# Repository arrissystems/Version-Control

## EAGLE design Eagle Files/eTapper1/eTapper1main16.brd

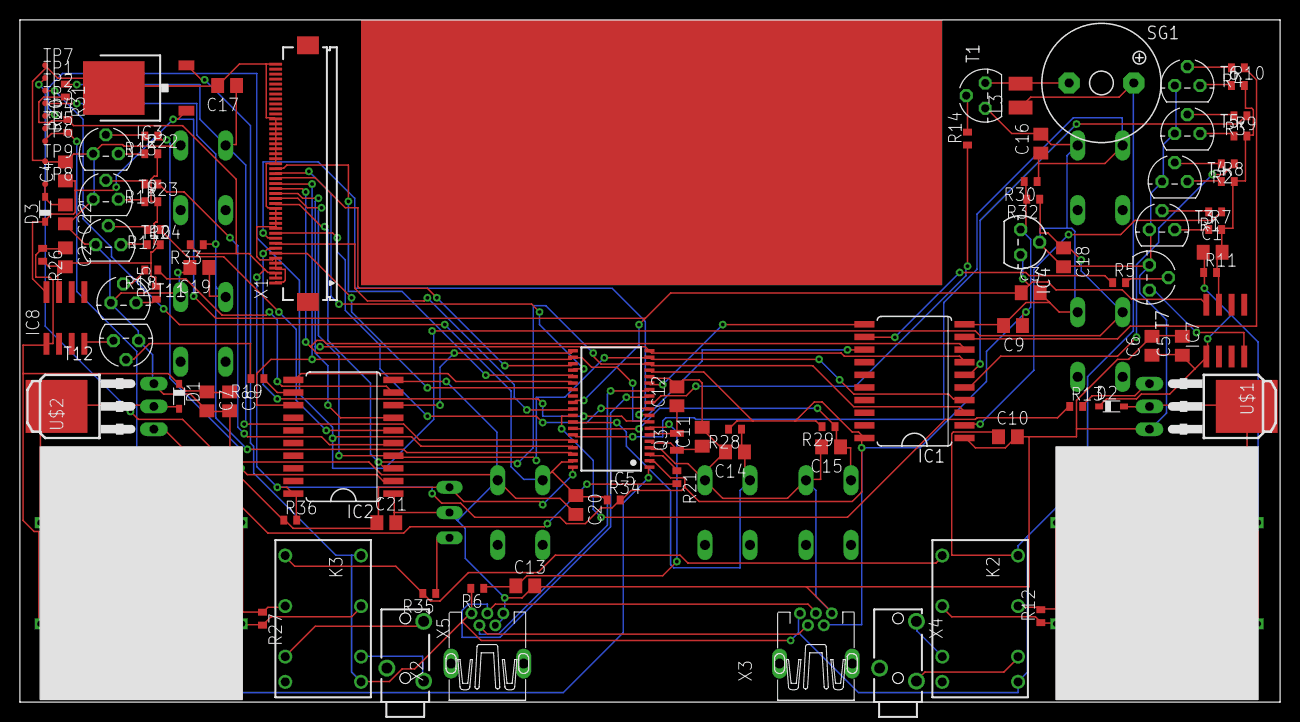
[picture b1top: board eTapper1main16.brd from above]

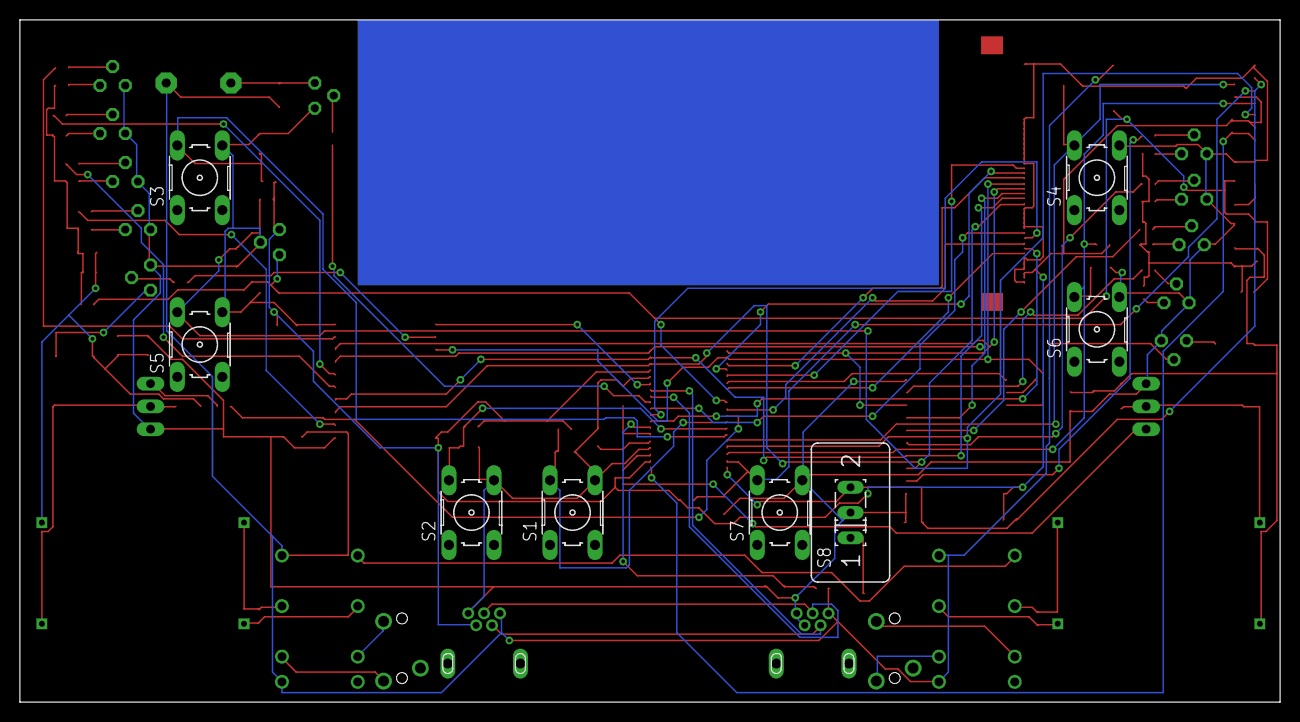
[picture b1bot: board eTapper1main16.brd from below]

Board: 2 copper layers, 126.7 x 68.6 mm, 110 parts (8 on the bottom side), 87 nets.

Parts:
C1, C2: .01uF; C0805
C3, C4: C0805
C5, C8: 3.3uF; C0805
C6, C7, C22: 220uF; C0805
C9, C10: 47uF; C0805
C11, C12: 12pF; C0805
C13: 1 uF; C0805
C14, C15, C16, C17, C18, C19, C20, C21: .1uF; C0805
D1, D2, D3: BAT60J; SOD323_ST
IC1, IC2: 74AC373DW; SO20W
IC3: LM2936DT-5.0; TO252
IC4: LM2936Z-3.0; TO92
IC5: MSP430F2232IDA; TSSOP38_R-PDSO-G38-DA
IC7, IC8: LP2951M; SO08
K2, K3: DF2-DC3V; DF2
L3: 470uH; L2825P
Q3: FC-12M
R1, R2, R3, R5, R6, R15, R16, R17, R18, R19, R20, R28, R29, R30, R31, R32, R33, R34, R36: 47K; R0402
R4: R0402
R7, R13, R14, R21, R22: 1K; R0402
R8, R11, R23, R26: 3K; R0402
R9, R24: 6K; R0402
R10, R25: 12K; R0402
R12, R27: 51K; R0402
R35: 100; R0402
S1, S2, S3, S4, S5, S6, S7: B3F-10XX
S8: M251
SG1: F/QMBIII
T1, T2, T3, T4, T5, T6, T7, T9, T10, T11, T12: 2N3904; TO92
TP1, TP2, TP3, TP4, TP5, TP6, TP7, TP8, TP9: TPSTP06R; TP06R
U$1, U$2: IRLR024N; I-PAK_TO251AA
U$3, U$4: XFMR
X1: FH12-45S-0.5SH
X2, X3: MINI-USB_SHIELD5P2-32005-601; 32005-601
X4, X5: 1501_03

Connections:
+3V: C9.1, IC1.20, IC2.20, IC4.1, IC5.2, IC5.16, R20.2, R28.2, R29.2, R30.2, R31.2, R32.2, R33.2, R34.2, R36.2, TP5.TP, X1.2, X1.3, X3.4
+9V: C3.1, C4.1, D3.C, IC3.1, IC4.3, IC5.28, IC7.8, IC8.8
/LCS: IC5.8, X1.8
/RST: C13.1, IC5.7, R6.1
BAT+: C22.1, D3.A, TP8.TP
GND: C3.2, C4.2, C5.2, C6.2, C7.2, C8.2, C9.2, C10.2, C11.2, C12.2, C13.2, C14.2, C15.2, C16.2, C17.2, C18.2, C19.2, C20.2, C21.2, C22.2, IC1.1, IC1.10, IC2.1, IC2.10, IC3.2, IC4.2, IC5.4, IC5.15, S1.4, S2.4, S3.4, S4.4, S5.4, S6.4, S7.4, S8.2, T1.3, T2.3, T3.3, T4.3, T5.3, T6.3, T7.3, T9.3, T10.3, T11.3, T12.3, TP7.TP, TP9.TP, U$1.3, U$2.3, X1.1, X1.4, X1.5, X1.6, X1.12, X1.13, X1.14, X1.15, X1.16, X1.25, X1.26, X1.27, X1.28, X1.29, X1.30, X1.31, X1.32, X1.33, X1.34, X1.45, X2.4, X2.5, X3.5
IO1_0: C14.1, IC5.31, R28.1, S1.2
IO1_1: C15.1, IC5.32, R29.1, S2.2
IO1_2: C16.1, IC5.33, R30.1, S3.2
IO1_3: C17.1, IC5.34, R31.1, S4.2
IO4_0: IC1.3, IC2.3, IC5.17, X1.17
IO4_1: IC1.4, IC2.4, IC5.18, X1.18
IO4_2: IC1.7, IC2.7, IC5.19, X1.19
IO4_3: IC1.8, IC2.8, IC5.20, X1.20
IO4_4: IC1.13, IC2.13, IC5.21, X1.21
IO4_5: IC5.22, X1.22
IO4_6: IC5.23, X1.23
IO4_7: IC5.24, X1.24
J2_1: K2.3, R12.1, U$3.P$3
J2_3: K2.10, R12.2, U$3.P$4
J3_1: K3.3, R27.1, U$4.P$3
J3_3: K3.10, R27.2, U$4.P$4
LD_/C: IC5.29, X1.9
LHVTRIG: IC5.30, R13.1
LRD: IC5.10, X1.11
LRESET: IC5.26, X1.7
LTS+: K2.8, X4.1
LTS-: K2.5, X4.3
LVSEL: IC1.11, IC5.14
LWR: IC5.9, X1.10
unnamed: IC1.2, R1.1
unnamed: IC1.5, R2.1
unnamed: IC1.6, R3.1
unnamed: IC1.9, R4.1
unnamed: IC1.12, R5.1
unnamed: L3.2, SG1.-, T1.1
unnamed: R4.2, T6.2
unnamed: R5.2, T7.2
unnamed: D2.A, U$1.2, U$1.4, U$3.P$1
unnamed: R7.1, T3.1
unnamed: R8.1, T4.1
unnamed: R9.1, T5.1
unnamed: R1.2, T3.2
unnamed: R2.2, T4.2
unnamed: R3.2, T5.2
unnamed: R10.1, T6.1
unnamed: C1.2, IC7.7, R7.2, R8.2, R9.2, R10.2, R11.2
unnamed: C1.1, C5.1, C6.1, D2.C, IC7.1, R11.1, U$3.P$2
unnamed: D1.A, U$2.2, U$2.4, U$4.P$1
unnamed: IC2.2, R15.1
unnamed: R13.2, U$1.1
unnamed: R14.2, T1.2
unnamed: R35.1, S8.1
unnamed: IC2.5, R16.1
unnamed: IC2.6, R17.1
unnamed: IC2.9, R18.1
unnamed: IC2.12, R19.1
unnamed: R15.2, T2.2
unnamed: R16.2, T9.2
unnamed: R17.2, T10.2
unnamed: R18.2, T11.2
unnamed: R19.2, T12.2
unnamed: K2.1, K3.1, R35.2
unnamed: R22.1, T2.1
unnamed: R23.1, T9.1
unnamed: R24.1, T10.1
unnamed: R25.1, T11.1
unnamed: C2.2, IC8.7, R22.2, R23.2, R24.2, R25.2, R26.2
unnamed: C2.1, C7.1, C8.1, D1.C, IC8.1, R26.1, U$4.P$2
unnamed: R21.2, U$2.1
unnamed: IC7.4, T7.1
unnamed: IC8.4, T12.1
RHVTRIG: IC5.3, R21.1
RTS+: K3.8, X5.1
RTS-: K3.5, X5.3
RVSEL: IC2.11, IC5.25
SCL: IC5.13, X2.2, X3.2
SDA: IC5.12, X2.3, X3.3
SPKR: IC5.11, R14.1
TCK: C18.1, IC5.35, R32.1, S5.2, TP4.TP
TDI: C20.1, IC5.37, R34.1, S7.2, TP2.TP
TDO: C21.1, IC5.38, R36.1, S8.3, TP1.TP
TEST: IC5.1, R20.1, TP6.TP
TMS: C19.1, IC5.36, R33.1, S6.2, TP3.TP
VCC: C10.1, IC3.3, K2.7, K2.12, K3.7, K3.12, L3.1, R6.2, SG1.+, X2.1, X3.1
XIN: C12.1, IC5.6, Q3.2
XOUT: C11.1, IC5.5, Q3.1
